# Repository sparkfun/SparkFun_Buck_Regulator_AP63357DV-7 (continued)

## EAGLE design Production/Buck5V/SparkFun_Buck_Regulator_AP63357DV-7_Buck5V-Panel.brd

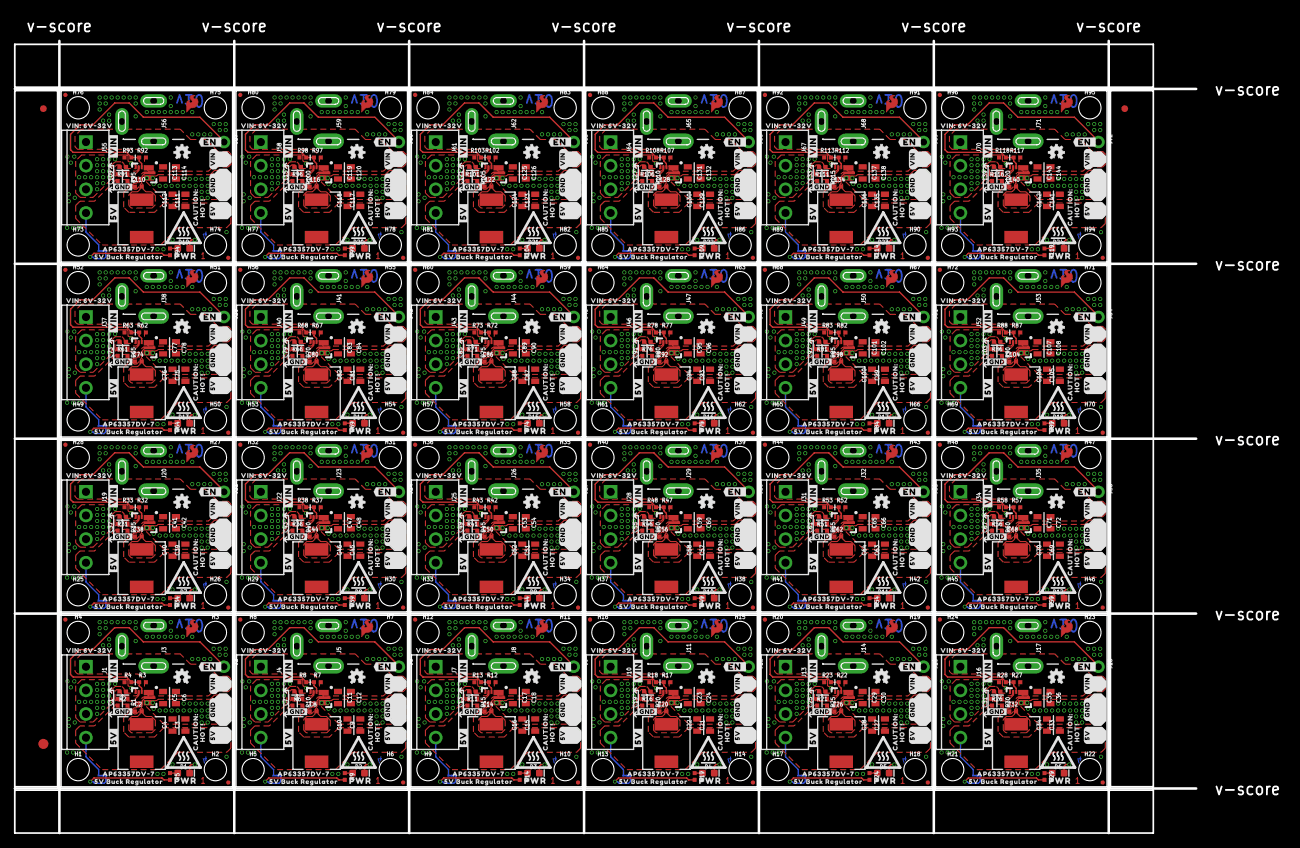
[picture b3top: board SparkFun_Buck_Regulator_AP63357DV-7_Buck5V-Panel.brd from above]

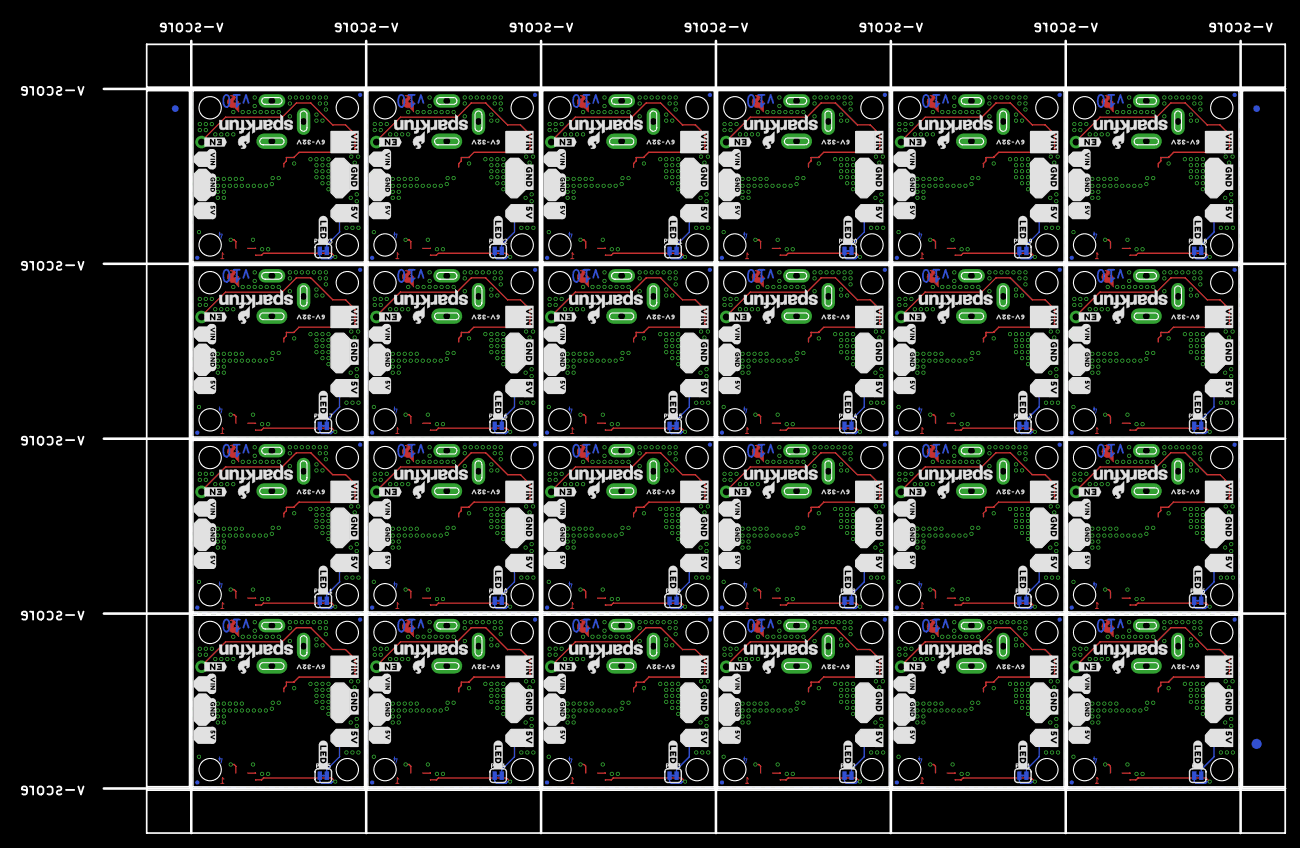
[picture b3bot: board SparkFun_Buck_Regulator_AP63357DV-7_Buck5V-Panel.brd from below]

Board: 4 copper layers, 175.0 x 117.3 mm, 1254 parts (315 on the bottom side), 216 nets.

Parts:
C1, C7, C13, C19, C25, C31, C37, C43, C49, C55, C61, C67, C73, C79, C85, C91, C97, C103, C109, C115, C121, C127, C133, C139: 47pF; 0402-TIGHT
C2, C8, C14, C20, C26, C32, C38, C44, C50, C56, C62, C68, C74, C80, C86, C92, C98, C104, C110, C116, C122, C128, C134, C140: 0.1uF; 0402-TIGHT
C3, C4, C9, C10, C15, C16, C21, C22, C27, C28, C33, C34, C39, C40, C45, C46, C51, C52, C57, C58, C63, C64, C69, C70, C75, C76, C81, C82, C87, C88, C93, C94, C99, C100, C105, C106, C111, C112, C117, C118, C123, C124, C129, C130, C135, C136, C141, C142: 22uF; 0805
C5, C6, C11, C12, C17, C18, C23, C24, C29, C30, C35, C36, C41, C42, C47, C48, C53, C54, C59, C60, C65, C66, C71, C72, C77, C78, C83, C84, C89, C90, C95, C96, C101, C102, C107, C108, C113, C114, C119, C120, C125, C126, C131, C132, C137, C138, C143, C144: 4.7uF; 0805
D1, D2, D3, D4, D5, D6, D7, D8, D9, D10, D11, D12, D13, D14, D15, D16, D17, D18, D19, D20, D21, D22, D23, D24: RED; LED-0603
E$1, E$2, E$3, E$4: FIDUCIAL-1X2
E$5, E$6: FIDUCIAL-1.5X3
FD1, FD2, FD3, FD4, FD5, FD6, FD7, FD8, FD9, FD10, FD11, FD12, FD13, FD14, FD15, FD16, FD17, FD18, FD19, FD20, FD21, FD22, FD23, FD24, FD25, FD26, FD27, FD28, FD29, FD30, FD31, FD32, FD33, FD34, FD35, FD36, FD37, FD38, FD39, FD40, FD41, FD42, FD43, FD44, FD45, FD46, FD47, FD48, FD49, FD50, FD51, FD52, FD53, FD54, FD55, FD56, FD57, FD58, FD59, FD60, FD61, FD62, FD63, FD64, FD65, FD66, FD67, FD68, FD69, FD70, FD71, FD72, FD73, FD74, FD75, FD76, FD77, FD78, FD79, FD80, FD81, FD82, FD83, FD84, FD85, FD86, FD87, FD88, FD89, FD90, FD91, FD92, FD93, FD94, FD95, FD96: FIDUCIALUFIDUCIAL; FIDUCIAL-MICRO
H1, H2, H3, H4, H5, H6, H7, H8, H9, H10, H11, H12, H13, H14, H15, H16, H17, H18, H19, H20, H21, H22, H23, H24, H25, H26, H27, H28, H29, H30, H31, H32, H33, H34, H35, H36, H37, H38, H39, H40, H41, H42, H43, H44, H45, H46, H47, H48, H49, H50, H51, H52, H53, H54, H55, H56, H57, H58, H59, H60, H61, H62, H63, H64, H65, H66, H67, H68, H69, H70, H71, H72, H73, H74, H75, H76, H77, H78, H79, H80, H81, H82, H83, H84, H85, H86, H87, H88, H89, H90, H91, H92, H93, H94, H95, H96: STAND-OFF
J1, J4, J7, J10, J13, J16, J19, J22, J25, J28, J31, J34, J37, J40, J43, J46, J49, J52, J55, J58, J61, J64, J67, J70: SCREWTERMINAL-3.5MM-4
J2, J6, J9, J12, J15, J18, J21, J24, J27, J30, J33, J36, J39, J42, J45, J48, J51, J54, J57, J60, J63, J66, J69, J72: 1X05_NO_SILK
J3, J5, J8, J11, J14, J17, J20, J23, J26, J29, J32, J35, J38, J41, J44, J47, J50, J53, J56, J59, J62, J65, J68, J71: POWER_JACK; POWER_JACK_PTH_SLOT_NO_OVRHNG_SILK
L1, L2, L3, L4, L5, L6, L7, L8, L9, L10, L11, L12, L13, L14, L15, L16, L17, L18, L19, L20, L21, L22, L23, L24: 6.8UH; 07A7_6U8H
LOGO1, LOGO3, LOGO5, LOGO7, LOGO9, LOGO11, LOGO13, LOGO15, LOGO17, LOGO19, LOGO21, LOGO23, LOGO25, LOGO27, LOGO29, LOGO31, LOGO33, LOGO35, LOGO37, LOGO39, LOGO41, LOGO43, LOGO45, LOGO47: OSHW-LOGOMINI; OSHW-LOGO-MINI
LOGO2, LOGO4, LOGO6, LOGO8, LOGO10, LOGO12, LOGO14, LOGO16, LOGO18, LOGO20, LOGO22, LOGO24, LOGO26, LOGO28, LOGO30, LOGO32, LOGO34, LOGO36, LOGO38, LOGO40, LOGO42, LOGO44, LOGO46, LOGO48: SFE_LOGO_NAME_FLAME.1_INCH; SFE_LOGO_NAME_FLAME_.1
PWR, PWR1, PWR2, PWR3, PWR4, PWR5, PWR6, PWR7, PWR8, PWR9, PWR10, PWR11, PWR12, PWR13, PWR14, PWR15, PWR16, PWR17, PWR18, PWR19, PWR20, PWR21, PWR22, PWR23: JUMPER-SMT_2_NC_TRACE_SILK; SMT-JUMPER_2_NC_TRACE_SILK
R1, R10, R15, R20, R25, R30, R35, R40, R45, R50, R55, R60, R65, R70, R75, R80, R85, R90, R95, R100, R105, R110, R115, R120: 220K; 0402-TIGHT
R2, R6, R11, R16, R21, R26, R31, R36, R41, R46, R51, R56, R61, R66, R71, R76, R81, R86, R91, R96, R101, R106, R111, R116: 41.2K; 0402-TIGHT
R3, R7, R12, R17, R22, R27, R32, R37, R42, R47, R52, R57, R62, R67, R72, R77, R82, R87, R92, R97, R102, R107, R112, R117: 93.1k; 0402-TIGHT
R4, R8, R13, R18, R23, R28, R33, R38, R43, R48, R53, R58, R63, R68, R73, R78, R83, R88, R93, R98, R103, R108, R113, R118: 22k; 0402-TIGHT
R5, R9, R14, R19, R24, R29, R34, R39, R44, R49, R54, R59, R64, R69, R74, R79, R84, R89, R94, R99, R104, R109, R114, R119: 2.2k; 0402-TIGHT
U1, U2, U3, U4, U5, U6, U7, U8, U9, U10, U11, U12, U13, U14, U15, U16, U17, U18, U19, U20, U21, U22, U23, U24: AP63357; V-DFN3020-13
U$1, U$25, U$50, U$74, U$98, U$122, U$146, U$170, U$194, U$218, U$242, U$266, U$290, U$314, U$338, U$362, U$386, U$410, U$434, U$458, U$482, U$506, U$530, U$554: AP63357DV#70
U$2, U$23, U$49, U$73, U$97, U$121, U$145, U$169, U$193, U$217, U$241, U$265, U$289, U$313, U$337, U$361, U$385, U$409, U$433, U$457, U$481, U$505, U$529, U$553: 5V_BUCK_REGULATOR0
U$3, U$43, U$67, U$91, U$115, U$139, U$163, U$187, U$211, U$235, U$259, U$283, U$307, U$331, U$355, U$379, U$403, U$427, U$451, U$475, U$499, U$523, U$547, U$571: #5V#4
U$4, U$44, U$68, U$92, U$116, U$140, U$164, U$188, U$212, U$236, U$260, U$284, U$308, U$332, U$356, U$380, U$404, U$428, U$452, U$476, U$500, U$524, U$548, U$572: #VIN#8
U$5, U$13, U$28, U$37, U$52, U$61, U$76, U$85, U$100, U$109, U$124, U$133, U$148, U$157, U$172, U$181, U$196, U$205, U$220, U$229, U$244, U$253, U$268, U$277, U$292, U$301, U$316, U$325, U$340, U$349, U$364, U$373, U$388, U$397, U$412, U$421, U$436, U$445, U$460, U$469, U$484, U$493, U$508, U$517, U$532, U$541, U$556, U$565: #VIN#0
U$6, U$7, U$38, U$39, U$62, U$63, U$86, U$87, U$110, U$111, U$134, U$135, U$158, U$159, U$182, U$183, U$206, U$207, U$230, U$231, U$254, U$255, U$278, U$279, U$302, U$303, U$326, U$327, U$350, U$351, U$374, U$375, U$398, U$399, U$422, U$423, U$446, U$447, U$470, U$471, U$494, U$495, U$518, U$519, U$542, U$543, U$566, U$567: #GND#0
U$8, U$19, U$27, U$31, U$51, U$55, U$75, U$79, U$99, U$103, U$123, U$127, U$147, U$151, U$171, U$175, U$195, U$199, U$219, U$223, U$243, U$247, U$267, U$271, U$291, U$295, U$315, U$319, U$339, U$343, U$363, U$367, U$387, U$391, U$411, U$415, U$435, U$439, U$459, U$463, U$483, U$487, U$507, U$511, U$531, U$535, U$555, U$559: #EN_#0
U$9, U$45, U$69, U$93, U$117, U$141, U$165, U$189, U$213, U$237, U$261, U$285, U$309, U$333, U$357, U$381, U$405, U$429, U$453, U$477, U$501, U$525, U$549, U$573: #GND#9
U$10, U$46, U$70, U$94, U$118, U$142, U$166, U$190, U$214, U$238, U$262, U$286, U$310, U$334, U$358, U$382, U$406, U$430, U$454, U$478, U$502, U$526, U$550, U$574: #5V#10
U$11, U$47, U$71, U$95, U$119, U$143, U$167, U$191, U$215, U$239, U$263, U$287, U$311, U$335, U$359, U$383, U$407, U$431, U$455, U$479, U$503, U$527, U$551, U$575: 6V#32V10
U$12, U$48, U$72, U$96, U$120, U$144, U$168, U$192, U$216, U$240, U$264, U$288, U$312, U$336, U$360, U$384, U$408, U$432, U$456, U$480, U$504, U$528, U$552, U$576: HOT##0
U$14, U$24, U$36, U$40, U$60, U$64, U$84, U$88, U$108, U$112, U$132, U$136, U$156, U$160, U$180, U$184, U$204, U$208, U$228, U$232, U$252, U$256, U$276, U$280, U$300, U$304, U$324, U$328, U$348, U$352, U$372, U$376, U$396, U$400, U$420, U$424, U$444, U$448, U$468, U$472, U$492, U$496, U$516, U$520, U$540, U$544, U$564, U$568: #5V#0
U$15, U$32, U$56, U$80, U$104, U$128, U$152, U$176, U$200, U$224, U$248, U$272, U$296, U$320, U$344, U$368, U$392, U$416, U$440, U$464, U$488, U$512, U$536, U$560: #LED_#0
U$16, U$41, U$65, U$89, U$113, U$137, U$161, U$185, U$209, U$233, U$257, U$281, U$305, U$329, U$353, U$377, U$401, U$425, U$449, U$473, U$497, U$521, U$545, U$569: CAUTION#0
U$17, U$29, U$53, U$77, U$101, U$125, U$149, U$173, U$197, U$221, U$245, U$269, U$293, U$317, U$341, U$365, U$389, U$413, U$437, U$461, U$485, U$509, U$533, U$557: SFE_LOGO_FLAME_COPPER_EXPOSED_.1
U$18, U$30, U$54, U$78, U$102, U$126, U$150, U$174, U$198, U$222, U$246, U$270, U$294, U$318, U$342, U$366, U$390, U$414, U$438, U$462, U$486, U$510, U$534, U$558: VIN#_6V#32V0
U$20, U$33, U$57, U$81, U$105, U$129, U$153, U$177, U$201, U$225, U$249, U$273, U$297, U$321, U$345, U$369, U$393, U$417, U$441, U$465, U$489, U$513, U$537, U$561: PWR0
U$21, U$34, U$58, U$82, U$106, U$130, U$154, U$178, U$202, U$226, U$250, U$274, U$298, U$322, U$346, U$370, U$394, U$418, U$442, U$466, U$490, U$514, U$538, U$562: #GND#1
U$22, U$35, U$59, U$83, U$107, U$131, U$155, U$179, U$203, U$227, U$251, U$275, U$299, U$323, U$347, U$371, U$395, U$419, U$443, U$467, U$491, U$515, U$539, U$563: HIGH_TEMP_WARNING
U$26, U$42, U$66, U$90, U$114, U$138, U$162, U$186, U$210, U$234, U$258, U$282, U$306, U$330, U$354, U$378, U$402, U$426, U$450, U$474, U$498, U$522, U$546, U$570: #VIN#3

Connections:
5V: C1.1, C3.1, C4.1, J1.4, J2.5, L1.P$2, PWR.2, R1.2
5V1: C7.1, C9.1, C10.1, J4.4, J6.5, L2.P$2, PWR1.2, R10.2
5V2: C13.1, C15.1, C16.1, J7.4, J9.5, L3.P$2, PWR2.2, R15.2
5V3: C19.1, C21.1, C22.1, J10.4, J12.5, L4.P$2, PWR3.2, R20.2
5V4: C25.1, C27.1, C28.1, J13.4, J15.5, L5.P$2, PWR4.2, R25.2
5V5: C31.1, C33.1, C34.1, J16.4, J18.5, L6.P$2, PWR5.2, R30.2
5V6: C37.1, C39.1, C40.1, J19.4, J21.5, L7.P$2, PWR6.2, R35.2
5V7: C43.1, C45.1, C46.1, J22.4, J24.5, L8.P$2, PWR7.2, R40.2
5V8: C49.1, C51.1, C52.1, J25.4, J27.5, L9.P$2, PWR8.2, R45.2
5V9: C55.1, C57.1, C58.1, J28.4, J30.5, L10.P$2, PWR9.2, R50.2
5V10: C61.1, C63.1, C64.1, J31.4, J33.5, L11.P$2, PWR10.2, R55.2
5V11: C67.1, C69.1, C70.1, J34.4, J36.5, L12.P$2, PWR11.2, R60.2
5V12: C73.1, C75.1, C76.1, J37.4, J39.5, L13.P$2, PWR12.2, R65.2
5V13: C79.1, C81.1, C82.1, J40.4, J42.5, L14.P$2, PWR13.2, R70.2
5V14: C85.1, C87.1, C88.1, J43.4, J45.5, L15.P$2, PWR14.2, R75.2
5V15: C91.1, C93.1, C94.1, J46.4, J48.5, L16.P$2, PWR15.2, R80.2
5V16: C97.1, C99.1, C100.1, J49.4, J51.5, L17.P$2, PWR16.2, R85.2
5V17: C103.1, C105.1, C106.1, J52.4, J54.5, L18.P$2, PWR17.2, R90.2
5V18: C109.1, C111.1, C112.1, J55.4, J57.5, L19.P$2, PWR18.2, R95.2
5V19: C115.1, C117.1, C118.1, J58.4, J60.5, L20.P$2, PWR19.2, R100.2
5V20: C121.1, C123.1, C124.1, J61.4, J63.5, L21.P$2, PWR20.2, R105.2
5V21: C127.1, C129.1, C130.1, J64.4, J66.5, L22.P$2, PWR21.2, R110.2
5V22: C133.1, C135.1, C136.1, J67.4, J69.5, L23.P$2, PWR22.2, R115.2
5V23: C139.1, C141.1, C142.1, J70.4, J72.5, L24.P$2, PWR23.2, R120.2
EN: J2.1, R3.1, R4.2, U1.P$2
EN1: J6.1, R7.1, R8.2, U2.P$2
EN2: J9.1, R12.1, R13.2, U3.P$2
EN3: J12.1, R17.1, R18.2, U4.P$2
EN4: J15.1, R22.1, R23.2, U5.P$2
EN5: J18.1, R27.1, R28.2, U6.P$2
EN6: J21.1, R32.1, R33.2, U7.P$2
EN7: J24.1, R37.1, R38.2, U8.P$2
EN8: J27.1, R42.1, R43.2, U9.P$2
EN9: J30.1, R47.1, R48.2, U10.P$2
EN10: J33.1, R52.1, R53.2, U11.P$2
EN11: J36.1, R57.1, R58.2, U12.P$2
EN12: J39.1, R62.1, R63.2, U13.P$2
EN13: J42.1, R67.1, R68.2, U14.P$2
EN14: J45.1, R72.1, R73.2, U15.P$2
EN15: J48.1, R77.1, R78.2, U16.P$2
EN16: J51.1, R82.1, R83.2, U17.P$2
EN17: J54.1, R87.1, R88.2, U18.P$2
EN18: J57.1, R92.1, R93.2, U19.P$2
EN19: J60.1, R97.1, R98.2, U20.P$2
EN20: J63.1, R102.1, R103.2, U21.P$2
EN21: J66.1, R107.1, R108.2, U22.P$2
EN22: J69.1, R112.1, R113.2, U23.P$2
EN23: J72.1, R117.1, R118.2, U24.P$2
FB: C1.2, R1.1, R2.2, U1.P$3
FB1: C7.2, R6.2, R10.1, U2.P$3
FB2: C13.2, R11.2, R15.1, U3.P$3
FB3: C19.2, R16.2, R20.1, U4.P$3
FB4: C25.2, R21.2, R25.1, U5.P$3
FB5: C31.2, R26.2, R30.1, U6.P$3
FB6: C37.2, R31.2, R35.1, U7.P$3
FB7: C43.2, R36.2, R40.1, U8.P$3
FB8: C49.2, R41.2, R45.1, U9.P$3
FB9: C55.2, R46.2, R50.1, U10.P$3
FB10: C61.2, R51.2, R55.1, U11.P$3
FB11: C67.2, R56.2, R60.1, U12.P$3
FB12: C73.2, R61.2, R65.1, U13.P$3
FB13: C79.2, R66.2, R70.1, U14.P$3
FB14: C85.2, R71.2, R75.1, U15.P$3
FB15: C91.2, R76.2, R80.1, U16.P$3
FB16: C97.2, R81.2, R85.1, U17.P$3
FB17: C103.2, R86.2, R90.1, U18.P$3
FB18: C109.2, R91.2, R95.1, U19.P$3
FB19: C115.2, R96.2, R100.1, U20.P$3
FB20: C121.2, R101.2, R105.1, U21.P$3
FB21: C127.2, R106.2, R110.1, U22.P$3
FB22: C133.2, R111.2, R115.1, U23.P$3
FB23: C139.2, R116.2, R120.1, U24.P$3
GND: C3.2, C4.2, C5.2, C6.2, D1.C, J1.2, J1.3, J2.3, J2.4, J3.GND, R2.1, R4.1, U1.P$4, U1.P$8
GND1: C9.2, C10.2, C11.2, C12.2, D2.C, J4.2, J4.3, J5.GND, J6.3, J6.4, R6.1, R8.1, U2.P$4, U2.P$8
GND2: C15.2, C16.2, C17.2, C18.2, D3.C, J7.2, J7.3, J8.GND, J9.3, J9.4, R11.1, R13.1, U3.P$4, U3.P$8
GND3: C21.2, C22.2, C23.2, C24.2, D4.C, J10.2, J10.3, J11.GND, J12.3, J12.4, R16.1, R18.1, U4.P$4, U4.P$8
GND4: C27.2, C28.2, C29.2, C30.2, D5.C, J13.2, J13.3, J14.GND, J15.3, J15.4, R21.1, R23.1, U5.P$4, U5.P$8
GND5: C33.2, C34.2, C35.2, C36.2, D6.C, J16.2, J16.3, J17.GND, J18.3, J18.4, R26.1, R28.1, U6.P$4, U6.P$8
GND6: C39.2, C40.2, C41.2, C42.2, D7.C, J19.2, J19.3, J20.GND, J21.3, J21.4, R31.1, R33.1, U7.P$4, U7.P$8
GND7: C45.2, C46.2, C47.2, C48.2, D8.C, J22.2, J22.3, J23.GND, J24.3, J24.4, R36.1, R38.1, U8.P$4, U8.P$8
GND8: C51.2, C52.2, C53.2, C54.2, D9.C, J25.2, J25.3, J26.GND, J27.3, J27.4, R41.1, R43.1, U9.P$4, U9.P$8
GND9: C57.2, C58.2, C59.2, C60.2, D10.C, J28.2, J28.3, J29.GND, J30.3, J30.4, R46.1, R48.1, U10.P$4, U10.P$8
GND10: C63.2, C64.2, C65.2, C66.2, D11.C, J31.2, J31.3, J32.GND, J33.3, J33.4, R51.1, R53.1, U11.P$4, U11.P$8
GND11: C69.2, C70.2, C71.2, C72.2, D12.C, J34.2, J34.3, J35.GND, J36.3, J36.4, R56.1, R58.1, U12.P$4, U12.P$8
GND12: C75.2, C76.2, C77.2, C78.2, D13.C, J37.2, J37.3, J38.GND, J39.3, J39.4, R61.1, R63.1, U13.P$4, U13.P$8
GND13: C81.2, C82.2, C83.2, C84.2, D14.C, J40.2, J40.3, J41.GND, J42.3, J42.4, R66.1, R68.1, U14.P$4, U14.P$8
GND14: C87.2, C88.2, C89.2, C90.2, D15.C, J43.2, J43.3, J44.GND, J45.3, J45.4, R71.1, R73.1, U15.P$4, U15.P$8
GND15: C93.2, C94.2, C95.2, C96.2, D16.C, J46.2, J46.3, J47.GND, J48.3, J48.4, R76.1, R78.1, U16.P$4, U16.P$8
GND16: C99.2, C100.2, C101.2, C102.2, D17.C, J49.2, J49.3, J50.GND, J51.3, J51.4, R81.1, R83.1, U17.P$4, U17.P$8
GND17: C105.2, C106.2, C107.2, C108.2, D18.C, J52.2, J52.3, J53.GND, J54.3, J54.4, R86.1, R88.1, U18.P$4, U18.P$8
GND18: C111.2, C112.2, C113.2, C114.2, D19.C, J55.2, J55.3, J56.GND, J57.3, J57.4, R91.1, R93.1, U19.P$4, U19.P$8
GND19: C117.2, C118.2, C119.2, C120.2, D20.C, J58.2, J58.3, J59.GND, J60.3, J60.4, R96.1, R98.1, U20.P$4, U20.P$8
GND20: C123.2, C124.2, C125.2, C126.2, D21.C, J61.2, J61.3, J62.GND, J63.3, J63.4, R101.1, R103.1, U21.P$4, U21.P$8
GND21: C129.2, C130.2, C131.2, C132.2, D22.C, J64.2, J64.3, J65.GND, J66.3, J66.4, R106.1, R108.1, U22.P$4, U22.P$8
GND22: C135.2, C136.2, C137.2, C138.2, D23.C, J67.2, J67.3, J68.GND, J69.3, J69.4, R111.1, R113.1, U23.P$4, U23.P$8
GND23: C141.2, C142.2, C143.2, C144.2, D24.C, J70.2, J70.3, J71.GND, J72.3, J72.4, R116.1, R118.1, U24.P$4, U24.P$8
unnamed: C8.1, U2.P$6
unnamed: D1.A, R5.1
unnamed: D2.A, R9.1
unnamed: C2.1, U1.P$6
unnamed: PWR.1, R5.2
unnamed: PWR1.1, R9.2
unnamed: C14.1, U3.P$6
unnamed: D3.A, R14.1
unnamed: PWR2.1, R14.2
unnamed: C20.1, U4.P$6
unnamed: D4.A, R19.1
unnamed: PWR3.1, R19.2
unnamed: C26.1, U5.P$6
unnamed: D5.A, R24.1
unnamed: PWR4.1, R24.2
unnamed: C32.1, U6.P$6
unnamed: D6.A, R29.1
unnamed: PWR5.1, R29.2
unnamed: C38.1, U7.P$6
unnamed: D7.A, R34.1
unnamed: PWR6.1, R34.2
unnamed: C44.1, U8.P$6
unnamed: D8.A, R39.1
unnamed: PWR7.1, R39.2
unnamed: C50.1, U9.P$6
unnamed: D9.A, R44.1
unnamed: PWR8.1, R44.2
unnamed: C56.1, U10.P$6
unnamed: D10.A, R49.1
unnamed: PWR9.1, R49.2
unnamed: C62.1, U11.P$6
unnamed: D11.A, R54.1
unnamed: PWR10.1, R54.2
unnamed: C68.1, U12.P$6
unnamed: D12.A, R59.1
unnamed: PWR11.1, R59.2
unnamed: C74.1, U13.P$6
unnamed: D13.A, R64.1
unnamed: PWR12.1, R64.2
unnamed: C80.1, U14.P$6
unnamed: D14.A, R69.1
unnamed: PWR13.1, R69.2
unnamed: C86.1, U15.P$6
unnamed: D15.A, R74.1
unnamed: PWR14.1, R74.2
unnamed: C92.1, U16.P$6
unnamed: D16.A, R79.1
unnamed: PWR15.1, R79.2
unnamed: C98.1, U17.P$6
unnamed: D17.A, R84.1
unnamed: PWR16.1, R84.2
unnamed: C104.1, U18.P$6
unnamed: D18.A, R89.1
unnamed: PWR17.1, R89.2
unnamed: C110.1, U19.P$6
unnamed: D19.A, R94.1
unnamed: PWR18.1, R94.2
unnamed: C116.1, U20.P$6
unnamed: D20.A, R99.1
unnamed: PWR19.1, R99.2
unnamed: C122.1, U21.P$6
unnamed: D21.A, R104.1
unnamed: PWR20.1, R104.2
unnamed: C128.1, U22.P$6
unnamed: D22.A, R109.1
unnamed: PWR21.1, R109.2
unnamed: C134.1, U23.P$6
unnamed: D23.A, R114.1
unnamed: PWR22.1, R114.2
unnamed: C140.1, U24.P$6
unnamed: D24.A, R119.1
unnamed: PWR23.1, R119.2
SW: C2.2, L1.P$1, U1.P$7, U1.P$9
SW1: C8.2, L2.P$1, U2.P$7, U2.P$9
SW2: C14.2, L3.P$1, U3.P$7, U3.P$9
SW3: C20.2, L4.P$1, U4.P$7, U4.P$9
SW4: C26.2, L5.P$1, U5.P$7, U5.P$9
SW5: C32.2, L6.P$1, U6.P$7, U6.P$9
SW6: C38.2, L7.P$1, U7.P$7, U7.P$9
SW7: C44.2, L8.P$1, U8.P$7, U8.P$9
SW8: C50.2, L9.P$1, U9.P$7, U9.P$9
SW9: C56.2, L10.P$1, U10.P$7, U10.P$9
SW10: C62.2, L11.P$1, U11.P$7, U11.P$9
SW11: C68.2, L12.P$1, U12.P$7, U12.P$9
SW12: C74.2, L13.P$1, U13.P$7, U13.P$9
SW13: C80.2, L14.P$1, U14.P$7, U14.P$9
SW14: C86.2, L15.P$1, U15.P$7, U15.P$9
SW15: C92.2, L16.P$1, U16.P$7, U16.P$9
SW16: C98.2, L17.P$1, U17.P$7, U17.P$9
SW17: C104.2, L18.P$1, U18.P$7, U18.P$9
SW18: C110.2, L19.P$1, U19.P$7, U19.P$9
SW19: C116.2, L20.P$1, U20.P$7, U20.P$9
SW20: C122.2, L21.P$1, U21.P$7, U21.P$9
SW21: C128.2, L22.P$1, U22.P$7, U22.P$9
SW22: C134.2, L23.P$1, U23.P$7, U23.P$9
SW23: C140.2, L24.P$1, U24.P$7, U24.P$9
VIN: C5.1, C6.1, J1.1, J2.2, J3.PWR, R3.2, U1.P$1
VIN1: C11.1, C12.1, J4.1, J5.PWR, J6.2, R7.2, U2.P$1
VIN2: C17.1, C18.1, J7.1, J8.PWR, J9.2, R12.2, U3.P$1
VIN3: C23.1, C24.1, J10.1, J11.PWR, J12.2, R17.2, U4.P$1
VIN4: C29.1, C30.1, J13.1, J14.PWR, J15.2, R22.2, U5.P$1
VIN5: C35.1, C36.1, J16.1, J17.PWR, J18.2, R27.2, U6.P$1
VIN6: C41.1, C42.1, J19.1, J20.PWR, J21.2, R32.2, U7.P$1
VIN7: C47.1, C48.1, J22.1, J23.PWR, J24.2, R37.2, U8.P$1
VIN8: C53.1, C54.1, J25.1, J26.PWR, J27.2, R42.2, U9.P$1
VIN9: C59.1, C60.1, J28.1, J29.PWR, J30.2, R47.2, U10.P$1
VIN10: C65.1, C66.1, J31.1, J32.PWR, J33.2, R52.2, U11.P$1
VIN11: C71.1, C72.1, J34.1, J35.PWR, J36.2, R57.2, U12.P$1
VIN12: C77.1, C78.1, J37.1, J38.PWR, J39.2, R62.2, U13.P$1
VIN13: C83.1, C84.1, J40.1, J41.PWR, J42.2, R67.2, U14.P$1
VIN14: C89.1, C90.1, J43.1, J44.PWR, J45.2, R72.2, U15.P$1
VIN15: C95.1, C96.1, J46.1, J47.PWR, J48.2, R77.2, U16.P$1
VIN16: C101.1, C102.1, J49.1, J50.PWR, J51.2, R82.2, U17.P$1
VIN17: C107.1, C108.1, J52.1, J53.PWR, J54.2, R87.2, U18.P$1
VIN18: C113.1, C114.1, J55.1, J56.PWR, J57.2, R92.2, U19.P$1
VIN19: C119.1, C120.1, J58.1, J59.PWR, J60.2, R97.2, U20.P$1
VIN20: C125.1, C126.1, J61.1, J62.PWR, J63.2, R102.2, U21.P$1
VIN21: C131.1, C132.1, J64.1, J65.PWR, J66.2, R107.2, U22.P$1
VIN22: C137.1, C138.1, J67.1, J68.PWR, J69.2, R112.2, U23.P$1
VIN23: C143.1, C144.1, J70.1, J71.PWR, J72.2, R117.2, U24.P$1

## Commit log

2022-10-06 v01 completed, ready for shrinking to babybuck.
2022-10-10 Added BabyBuck design.
2022-10-10 Added dimensions, ordering instructions, set board stackup.
2022-10-10 Added AOI silk for separating R/Cs easier.
2022-10-10 Renumbered parts to match other schematic.
2022-10-12 v01 changes implemented.
    Schematic:
    Add note for LED jumper
    Add green wire for EN
    Section titles center anchor
    Rename Regulator section
    Layout:
2022-10-12 Slight component shuffling in prep for protos.
2022-10-12 Remove silk from Power Jack so no silk overhangs.
2022-10-12 Added gerbers for v01, added UVLO text to babybuck sch.
2022-10-21 Removed unused lib parts. Added PROD_IDs to parts. Updated sch/brd files.
2022-10-21 Swap POP for UnPOP'd connector.
2022-12-13 Ready for v10 reds.
    1x1 - Thicken silk border on U1
    micro - Move fiducial to increase heat sink size
    both - panelize
2022-12-16 Centered schematic section titles.
2022-12-19 Prepare for v10 reds order.
    Change R1/R2 to better match 5V output requirement.
    Repanelize.
    Reorganize Production Folder Structure.
2023-02-03 Reduce paste layer on buck. Repanelize.
2023-02-10 Update dimensions
    Updated dimension layer
    - Fixed incorrect measurement for heat sink pad
    - Used boundary measurement instead of center point to reduce clutter
2023-02-10 Update README.md
    Added content
2023-02-10 Remove
    Datasheet will be included with GitHub pages files
2023-02-10 Initial documentation commit
2023-02-10 Stylesheet changes
2023-02-10 Move Hard Copy page
    Move page to tab on right side and bottom of navigation, if tabs are disabled
    Renamed file to hard_copy
    Removed tabs.html file (needs to be in partials folder)
2023-02-10 Moved hard copy file
2023-02-10 Add GItHub pages build workflow
2023-02-10 Update MkDocs configurations
    Add favicon
    Update mkdocs configuration
2023-02-10 Fix links
2023-02-10 Fix single page view
    used old file name
2023-02-10 Fix content
2023-02-11 Update board dimension
    Move measurements for heat sink onto reference layer and add box outline
2023-02-11 Update Hookup Guide
    Include updated board dimensions
2023-02-11 Fix iframe
2023-02-11 Update README.md
    Add release tag
2023-02-16 Update images
    Change all elements to figure/figcaption
    Remove "click to enlarge" caption and use as the image title.
2023-02-16 Add product links
2023-02-16 Fix typos
2023-02-16 Update copyright
    For webpage and pdf
2023-02-16 Update pdf settings
2023-02-17 Quiescent Current
    Added documentation for the quiescent current draw, based on issue #1
2023-02-21 Stylesheet Update
    Stylesheet update to remove table borders for tables with "pdf" class
    - Defined in stylesheet instead of being declared for each table
2023-02-23 Update extra.css
    Add comment
2023-02-23 Update README.md
    update information
2023-02-23 Update README.md
    summarize information
2023-02-23 Update stylesheets
2023-02-28 Update troubleshooting_tips.md
    Add note for using batteries
2023-02-28 Update troubleshooting_tips.md
    Fix typo
    Add clarification for 18650s
2023-03-09 Correct enable pin info
    Added default configuration info
    Added information about bypassing UVLO
2023-03-09 Fix image link
2023-03-09 remove place holders
2023-03-09 grammatical fixes
2023-03-22 Update index.md
    Update to new standard
2023-03-22 File reorganization
    Moved overrides folder to appropriate location to populate icons
    Added javascript and stylesheets folders for those files
    Renames sfe_logo.svg to sfe-logo.svg
2023-03-22 Add Autodesk icon
2023-03-22 Add redirect
    Rename index page and add redirect
    This allows for the support of including section icons
2023-03-22 Add heart icon feature
    Adds hear icon feature
2023-03-22 Add icons to title pages
2023-03-22 Add typeset icons
2023-03-22 Update mkdocs.yml
    Update icon comments
2023-03-22 Redirect home icon
    Redirect icon to product page instead of home page
2023-03-22 Update issue/pr files
    Add icons
    Add markdown lint fixes
2023-03-22 Add QR codes
    Add QR codes for printed hard copies
2023-03-22 Update extra.css
    Update color
2023-03-22 Add READMEs
2023-03-22 New grid cards styling
    Automatically show grid cards
    Added a new class "hide" to hide grid card
2023-03-22 Update getting_started.md
    Turn jumper modification into admonition
2023-03-22 Change icons
2023-03-22 Edit mistakes
2023-03-22 Redo layout
2023-03-22 Hide video
    QR code should be added for print outs
2023-03-22 Enable JS
    Enable javascript for mathjax
2023-03-22 Update mkdocs.yml
    Add chrome installation
2023-03-22 Update mkdocs.yml
    Try workaround
2023-03-22 Update mkdocs.yml
    Fix indent
2023-03-22 Update mkdocs.yml
    add flag
2023-03-22 Disable JS
    Comment out changes
    Option and workaround failed
2023-04-14 Update extra.css
    fix color standard
2023-04-14 Update sfe-logo.svg
    fix viewbox
2023-04-14 New Buck Regs
    Add links for products and tutorial
2023-04-14 Update getting_started.md
    copy/pasta... fix wording
2023-04-14 Deployed d24fa11 with MkDocs version: 1.4.2
2025-01-08 Fix link
    Typo
2025-01-08 Update workflow
2025-01-08 Revert "Update workflow"
    This reverts commit afcf3f4b45c07d3d61a1329126f5fd33961dd625.
2025-01-08 Add thumbnail
2025-01-08 Deployed a44219f with MkDocs version: 1.6.1
2026-06-03 Deployed 2daeae4 with MkDocs version: 1.6.1
